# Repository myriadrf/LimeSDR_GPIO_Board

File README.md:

# LimeSDR GPIO Board

The [LimeSDR GPIO Board](https://myriadrf.org/projects/limesdr-gpio-board/) is an expansion board for the LimeSDR family that provides individually settable, bi-directional level-shifted I/O for FPGA GPIO 0-7. Each I/O has a high-voltage and power Darlington drive stage suitable for inductive loads, such as coaxial relays. 

* **Provides bi-directional level shifted IO for GPIO 0-7**
  * 1.2-5.5V IO on J2
* **Each IO has a high voltage and power Darlington drive stage**
  * Acceptable rating 30V 300mA (0-4) 200mA (5-7)
  * Suitable for inductive loads
* **Input/Output are individually switch-able**
* **LimeSDR form factor**
* **Individually pluggable relay connections**

## Contents

The directory structure is as follows:

      hardware/<variant>/<version>/
          Equivalent Circuits/
          Project Outputs/       - BOM, rule check reports, Gerbers, pick & place files, PDFs

      software/
          examples/		 - Simple software examples

## Changelog

| Version   | Date     | Summary
|-----------|----------|--------------------------
| 0402 CAD2 | 21/02/18 | First production version |

## Licence

LimeSDR GPIO Board copyright 2018 [AB Open Ltd](https://abopen.com).

<br />This work is licensed under a <a rel="license" href="http://creativecommons.org/licenses/by/4.0/">Creative Commons Attribution 4.0 International License</a>.

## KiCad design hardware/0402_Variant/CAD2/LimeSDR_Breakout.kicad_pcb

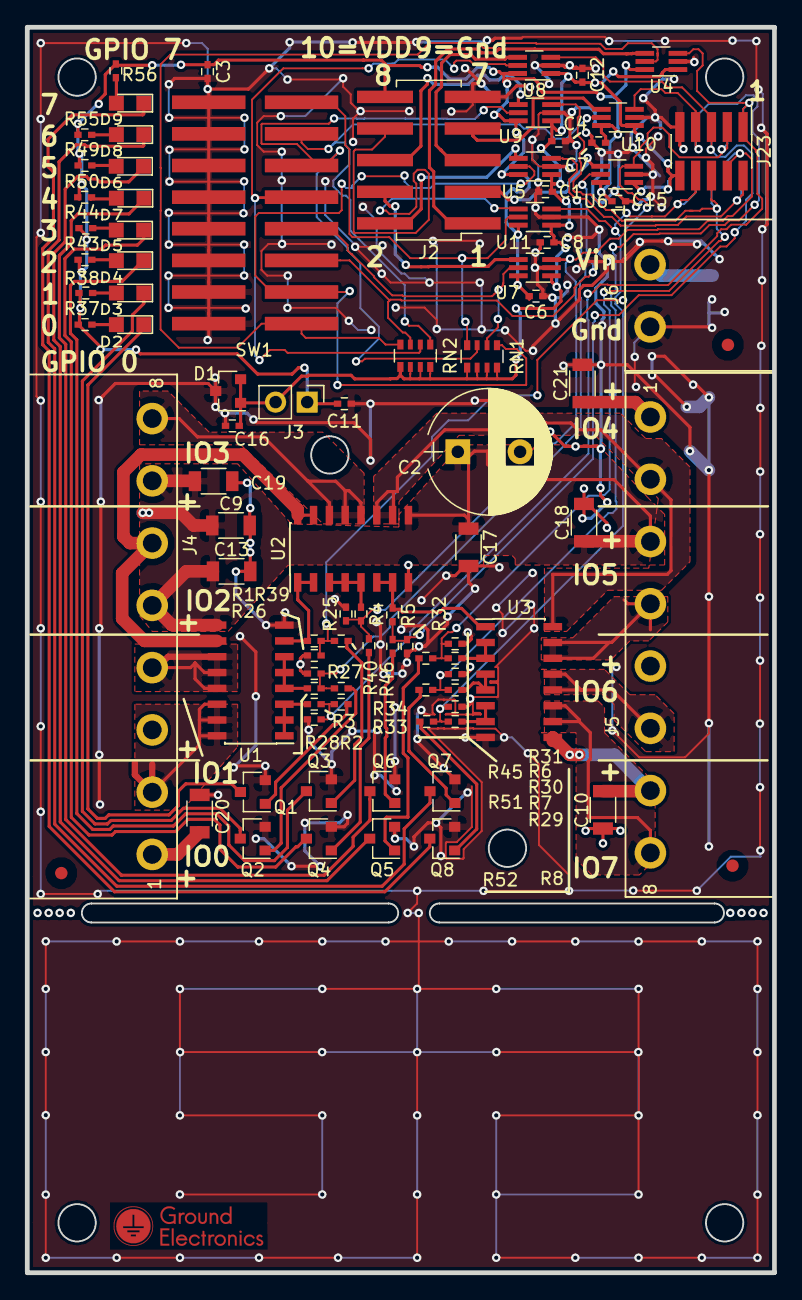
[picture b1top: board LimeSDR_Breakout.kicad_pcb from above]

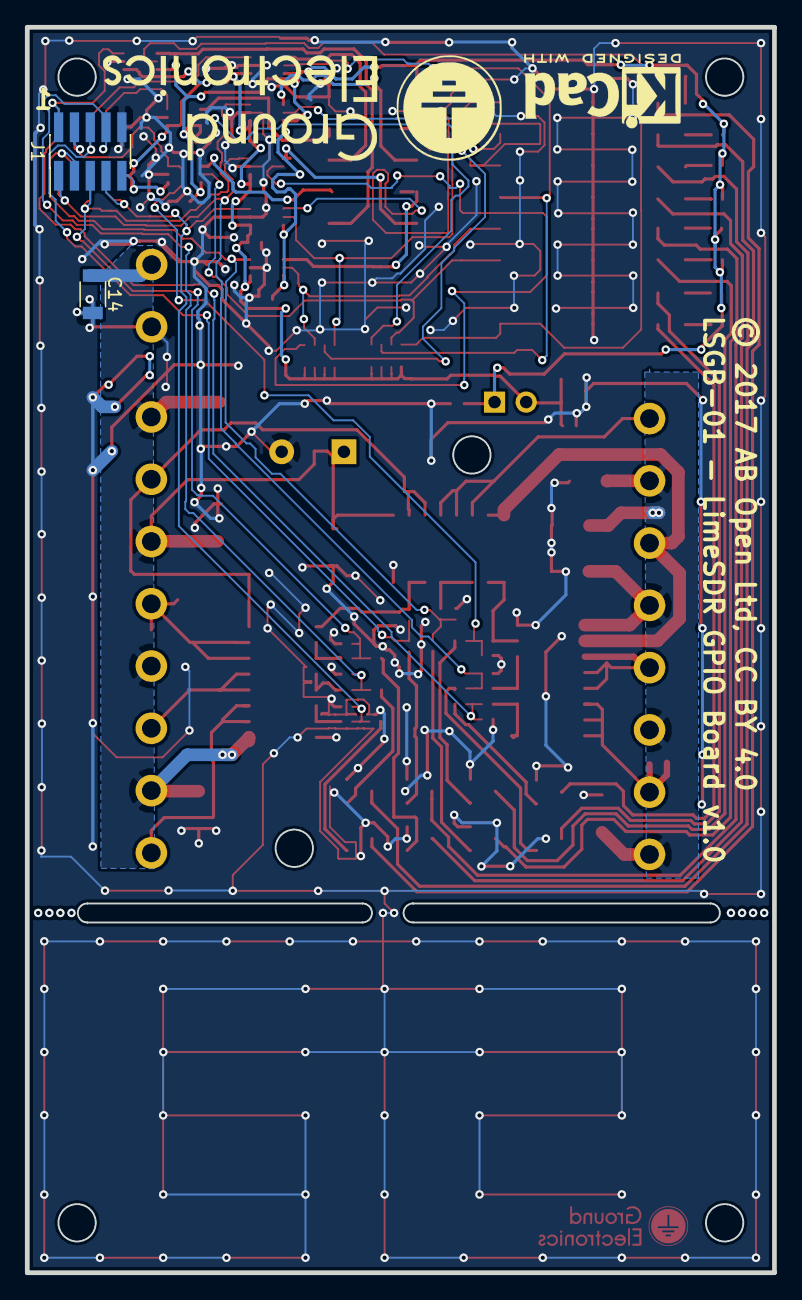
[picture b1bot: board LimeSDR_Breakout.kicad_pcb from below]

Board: 2 copper layers, 60.0 x 100.0 mm, 90 parts (2 on the bottom side), 68 nets.

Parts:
C1, C3, C4, C6, C7, C8, C11, C12, C15, C16: 1uF 16V 0402; C_0402
C2: CP; CP_Radial_D10.0mm_P5.00mm
C9, C10, C13, C17, C18, C19, C20, C21: 100nF 1206 50V; C_1206
C14: DNI; C_1206
D1: GS0T03C_SOT23; SOT-23
D2, D3, D4, D5, D6, D7, D8, D9: LED; LED_0805
J1, J23: CONN_02X05; Pin_Header_Straight_2x05_Pitch1.27mm_SMD
J2: CONN_02X05; Pin_Header_Straight_2x05_Pitch2.54mm_SMD
J3: CONN_01X02; Pin_Header_Straight_1x02_Pitch2.54mm
J4, J5: Screw_Terminal_1x08; RS_189_6060_R
J6: Screw_Terminal_1x02; RS_189-6105_reversed
Q1, Q2, Q3, Q4, Q5, Q6, Q7, Q8: BC847; SOT-23
R1, R2, R3, R4, R5, R6, R7, R8: 0R; C_0402
R25, R26, R27, R28, R29, R30, R31, R32: DNI; C_0402
R33, R34, R39, R40, R45, R46, R51, R52: 47k; C_0402
R37, R38, R43, R44, R49, R50, R55, R56: 220R; C_0402
RN1: 10K; R_Array_Convex_4x0603
RN2: 10k; R_Array_Convex_4x0603
SW1: DIP_8_SW_IKD0803101; DIP_W7.40_Gull-Wing-J
U1, U2, U3: ULN2003A; SOIC-16_3.9x9.9mm_Pitch1.27mm
U4, U5, U6, U7, U8, U9, U10, U11: 74LVC1T45; SOT-363_SC-70-6_Handsoldering

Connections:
+3V3: C1.1, C4.1, C8.1, C12.1, C16.1, D1.1, D1.2, J1.10, J3.2, J23.10, RN1.5, RN1.6, RN1.7, RN1.8, RN2.5, RN2.6, RN2.7, RN2.8, U4.1, U5.1, U6.1, U7.1, U8.1, U9.1, U10.1, U11.1
DIR_GPIO0: RN2.4, SW1.1, U4.5
DIR_GPIO1: RN1.1, SW1.2, U5.5
DIR_GPIO2: RN2.3, SW1.3, U6.5
DIR_GPIO3: RN1.2, SW1.4, U7.5
DIR_GPIO4: RN2.2, SW1.5, U8.5
DIR_GPIO5: RN1.3, SW1.6, U9.5
DIR_GPIO6: RN2.1, SW1.7, U10.5
DIR_GPIO7: RN1.4, SW1.8, U11.5
GND: C1.2, C2.2, C3.2, C4.2, C6.2, C7.2, C8.2, C9.2, C10.2, C11.2, C12.2, C13.2, C14.2, C15.2, C16.2, C17.2, C18.2, C19.2, C20.2, C21.2, D1.3, J1.9, J2.9, J6.2, J23.9, Q1.2, Q2.2, Q3.2, Q4.2, Q5.2, Q6.2, Q7.2, Q8.2, R25.2, R26.2, R27.2, R28.2, R29.2, R30.2, R31.2, R32.2, SW1.9, SW1.10, SW1.11, SW1.12, SW1.13, SW1.14, SW1.15, SW1.16, U1.8, U2.8, U3.8, U4.2, U5.2, U6.2, U7.2, U8.2, U9.2, U10.2, U11.2
GPIO0: J1.1, J23.1, R2.2, R28.1, R33.2, U4.3
GPIO0_LS: J2.1, U4.4
GPIO1: J1.2, J23.2, R3.2, R27.1, R34.2, U5.3
GPIO1_LS: J2.2, U5.4
GPIO2: J1.3, J23.3, R1.2, R26.1, R39.2, U6.3
GPIO2_LS: J2.3, U6.4
GPIO3: J1.4, J23.4, R4.2, R25.1, R40.2, U7.3
GPIO3_LS: J2.4, U7.4
GPIO4: J1.5, J23.5, R5.2, R32.1, R46.2, U8.3
GPIO4_LS: J2.5, U8.4
GPIO5: J1.6, J23.6, R6.2, R31.1, R45.2, U9.3
GPIO5_LS: J2.6, U9.4
GPIO6: J1.7, J23.7, R7.2, R30.1, R51.2, U10.3
GPIO6_LS: J2.7, U10.4
GPIO7: J1.8, J23.8, R8.2, R29.1, R52.2, U11.3
GPIO7_LS: J2.8, U11.4
unnamed: D2.1, Q1.3
unnamed: D2.2, R37.2
unnamed: D3.1, Q2.3
unnamed: D3.2, R38.2
unnamed: D4.1, Q3.3
unnamed: D4.2, R43.2
unnamed: D5.1, Q4.3
unnamed: D5.2, R44.2
unnamed: D6.1, Q5.3
unnamed: D6.2, R49.2
unnamed: D7.1, Q6.3
unnamed: D7.2, R50.2
unnamed: D8.1, Q7.3
unnamed: D8.2, R55.2
unnamed: D9.1, Q8.3
unnamed: D9.2, R56.2
unnamed: Q1.1, R33.1
unnamed: Q2.1, R34.1
unnamed: Q3.1, R39.1
unnamed: Q4.1, R40.1
unnamed: Q5.1, R45.1
unnamed: Q6.1, R46.1
unnamed: Q7.1, R51.1
unnamed: Q8.1, R52.1
unnamed: R1.1, U1.7, U2.1, U2.2
unnamed: R2.1, U1.1, U1.2, U1.3
unnamed: R3.1, U1.4, U1.5, U1.6
unnamed: R4.1, U2.3, U2.4, U2.5
unnamed: R5.1, U2.6, U2.7, U3.1
unnamed: R6.1, U3.2, U3.3
unnamed: R7.1, U3.4, U3.5
unnamed: R8.1, U3.6, U3.7
RELAY_0: J4.2, U1.14, U1.15, U1.16
RELAY_1: J4.4, U1.11, U1.12, U1.13
RELAY_2: J4.6, U1.10, U2.15, U2.16
RELAY_3: J4.8, U2.12, U2.13, U2.14
RELAY_4: J5.2, U2.10, U2.11, U3.16
RELAY_5: J5.4, U3.14, U3.15
RELAY_6: J5.6, U3.12, U3.13
RELAY_7: J5.8, U3.10, U3.11
VCOM: C2.1, C9.1, C10.1, C13.1, C14.1, C17.1, C18.1, C19.1, C20.1, C21.1, J4.1, J4.3, J4.5, J4.7, J5.1, J5.3, J5.5, J5.7, J6.1, U1.9, U2.9, U3.9
VDDA: C3.1, C6.1, C7.1, C11.1, C15.1, J2.10, J3.1, R37.1, R38.1, R43.1, R44.1, R49.1, R50.1, R55.1, R56.1, U4.6, U5.6, U6.6, U7.6, U8.6, U9.6, U10.6, U11.6

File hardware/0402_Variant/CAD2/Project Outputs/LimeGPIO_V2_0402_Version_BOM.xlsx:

Ref | Qnty | Kit 100 | Kit 60 | Kit QTY | Value | Footprint | Description | RS PN | ManfPN
C1, C3, C4, C6, C7, C8, C11, C12, C15, C16 | 10 | 1000 | 600 | Reel(90% Full) | 1uF 10V 0402 | 0402 | Unpolarized capacitor |  | C0402C105K8PAC7867
C2 | 1 | 100 | 60 | Bag 50 x2 | CP | TH | Polarised capacitor | 440-6575 | SK063M0100B5S-1012
C9, C10, C13, C17, C18, C19, C20, C21 | 8 | 800 | 480 | Reel(4000) | 100nF 1206 50V | 1206 | Unpolarized capacitor | 870-2776 | C1206C104K5RACTU
D1 | 1 | 100 | 60 | Reel(250) | GS0T03C_SOT23 | SOT23 | Bidirectional dual transient-voltage-suppression (TVS) diode (center=pin3) | 699-7957P | GSOT03C-E3-08
D2, D3, D4, D5, D6, D7, D8, D9 | 8 | 800 | 480 | Reel(4000) | LED | 0805 | LED generic (green) | 121-7785 | LG971
J23 | 1 | 100 | 60 | Tube 80 | CONN_02X05 | SM |  | 451-663 | FTSH-105-04-F-DV
J2 | 1 | 100 | 60 | Tube 120 | CONN_02X05 | SM |  |  | HTSS-105-01-T-DW
J3 | 1 | 100 | 60 | Bag 25x4 | CONN_01X02 | TH |  | 251-8086 | W81102T3825RC
J4, J5 | 2 | 200 | 120 | Box Loose x120 | Screw_Terminal_1x08 | TH |  | 189-6161 | 1757307
J6 | 1 | 100 | 60 | Bag loose 12x5 | Screw_Terminal_1x02 | TH |  | 189-6105 | 1757242
Q1, Q2, Q3, Q4, Q5, Q6, Q7, Q8 | 8 | 800 | 480 | Reel(90% Full) | BC847 | SOT23 | 45V Vce, 0.8A Ic, NPN, SOT-23 | 717-1578 | BC847C
R1, R2, R3, R4, R5, R6, R7, R8 | 8 | 800 | 480 | Reel(70% Full) | 0R | 0402 | Resistor |  | RC0402JR-070RL
R33, R34, R39, R40, R45, R46, R51, R52 | 8 | 800 | 480 | Reel(90% Full) | 47k | 0402 | Resistor |  | KMB-1610310072
R37, R38, R43, R44, R49, R50, R55, R56 | 8 | 800 | 480 | Reel(70% Full) | 220R | 0402 | Resistor |  | KMB-1701190047
RN1,RN2 | 1 | 100 | 60 | Reel(300) | 10K | 4x0603 | 4 Resistor network, parallel topology, DIP package | 426-229P | CAY16-103J4LF
SW1 | 1 | 100 | 60 | Tube 104 | DIP_8_SW_IKD0803101 | SM |  | 189-6010 | IKD0803101
U1, U2, U3 | 3 | 300 | 180 | Reelx2(200+200) | ULN2003A | SOIC | High Voltage, High Current Darlington Transistor Arrays | 251-8503 | ULN2003D1013TR
U4, U5, U6, U7, U8, U9, U10, U11 | 8 | 800 | 480 | Reel(3000) | 74LVC1T45 | SC70 – 6pin |  | 922-2385 | SN74LVC1T45DCKR

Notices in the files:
hardware/0402_Variant/CAD2/LimeSDR_Breakout.kicad_pcb:
© 2017 AB Open Ltd, CC BY 4.0
